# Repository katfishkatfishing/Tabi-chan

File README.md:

# Tabi-chan
>Our plan for Third Space Hack Club - Week 3!

A travel companion that tracks and logs your journey, and provides the weather data, and geo data.

## Project Overview
An adorable little travel companion that lives in a small device that has an e-ink display and a GPS sensor.

Tabi-chan (旅-chan) is a little gps sensor that you can clip onto yourself when out on a journey. She then sends over the tracked data to your phone via BLE and dislays it all on a web app. The basic features of the web app are route tracking, location overview, and weather overview. 

### <ins>Key Features of Box</ins> 
<ul style="margin-top: -5px; margin-bottom: 0; padding-left: 10px">
    <p style="margin-bottom: 5px">
        <b>GPS Tracking & Activity Logging</b>
    <ul style="padding-left: 45px">
        <p style="text-indent: -24px; margin-bottom: 5px">
            <b>GPS:</b> Calculate latitude, longitude and altitude.</p>
        <p style="text-indent: -24px; margin-bottom: 5px">
            <b>Route tracking:</b> Route tracking using Leaflet, calculates pace and distance</p>
        <p style="text-indent: -24px; margin-bottom: 5px">
            <b>Location Overview:</b> Query OpenStreetMap API to get current location.</p>
        <p style="text-indent: -24px; margin-bottom: 5px">
            <b>Weather Overview:</b> Uses Open-Meteo API to fetch weather info.</p>

### Say hi to Tabi-chan

## PCB
| Top | Bottom |
| --- | --- |
|  |  |

## Case

## BOM
| Reference | Value | Qty | Price | Source |
| :--- | :--- | :--- | :--- | :--- |
| U6 | IP5306-I2C | 1 | $0.35 | https://www.lcsc.com/product-detail/New-Arrivals_INJOINIC-IP5306-I2C_C488349.html |
| U5 | AP2112K-3.3TRG1 | 1 | $0.17 | https://jlcpcb.com/partdetail/AP2112K-3.3TRG1/C51118 |
| U2 | NEO-6M-0-001_C32413118 | 1 | $6.69 | https://jlcpcb.com/partdetail/UBLOX-NEO_6M_0001/C32413118 |
| U1 | ESP32-S3-WROOM-1(N16R8) | 1 | $3.79 | https://www.lcsc.com/product-detail/C2913202.html |
| SW1 | SW_Push | 1 | $0.02 | https://www.lcsc.com/product-detail/C318884.html |
| R12 | 1k | 1 | $0.0033 | https://www.lcsc.com/product-detail/C5362357.html |
| R8 | 2R | 1 | $0.21 | https://www.digikey.com/en/products/detail/vishay-dale/RCS08052R00FKEA/5868970 |
| R4,R5,R6,R7,R9,R10,R11 | 10k | 7 | $0.0029 | https://www.lcsc.com/product-detail/chip-resistor-surface-mount_tyohm-rmc-0603-10k-j-n_C5362358.html |
| R3 | 0.5R | 1 | $0.0013 | https://jlcpcb.com/partdetail/VO-SCR0603JR500/C3017643 |
| R1,R2 | 5.1k | 2 | $0.0016 | https://www.lcsc.com/product-detail/C23186.html |
| Q1,Q2 | BSS138BKW | 2 | RM1.10 | https://www.digikey.my/en/products/detail/nexperia-usa-inc/BSS138BKW-115/2779824 |
| L1 | 1uH | 1 | $0.0742 | https://jlcpcb.com/partdetail/YJYCOIN-YHNR30121R0M/C20416185 |
| J4 | Conn_01x08 | 1 | $0.0491 | https://www.lcsc.com/product-detail/C492407.html |
| J3 | Conn_01x02 | 1 | $0.0180 | https://www.lcsc.com/product-detail/C492401.html |
| J2 | U.FL | 1 | $0.1072 | https://www.lcsc.com/product-detail/C88374.html |
| J1 | USB_C_Receptacle_USB2.0_16P | 1 | $0.0415 | https://www.lcsc.com/product-detail/C2765186.html |
| C11,C12,C13 | 0.1uF | 3 | $0.0107 | https://www.lcsc.com/product-detail/C131394.html |
C8,C9,C10,C14 | 1uF | 4 | $0.1137 | https://jlcpcb.com/partdetail/KEMET-C0603C105K3RACTU/C2177372|
C6,C7,C15 | 10uF | 3 | $0.1027 | https://jlcpcb.com/partdetail/AIDECAPACITOR-0805X5R106M500NT/C49326683|
C1,C2,C3,C4,C5 | 22uF | 5 | $0.0844 | https://jlcpcb.com/partdetail/CCTC-TCC0805X5R226K160FT/C48885730|

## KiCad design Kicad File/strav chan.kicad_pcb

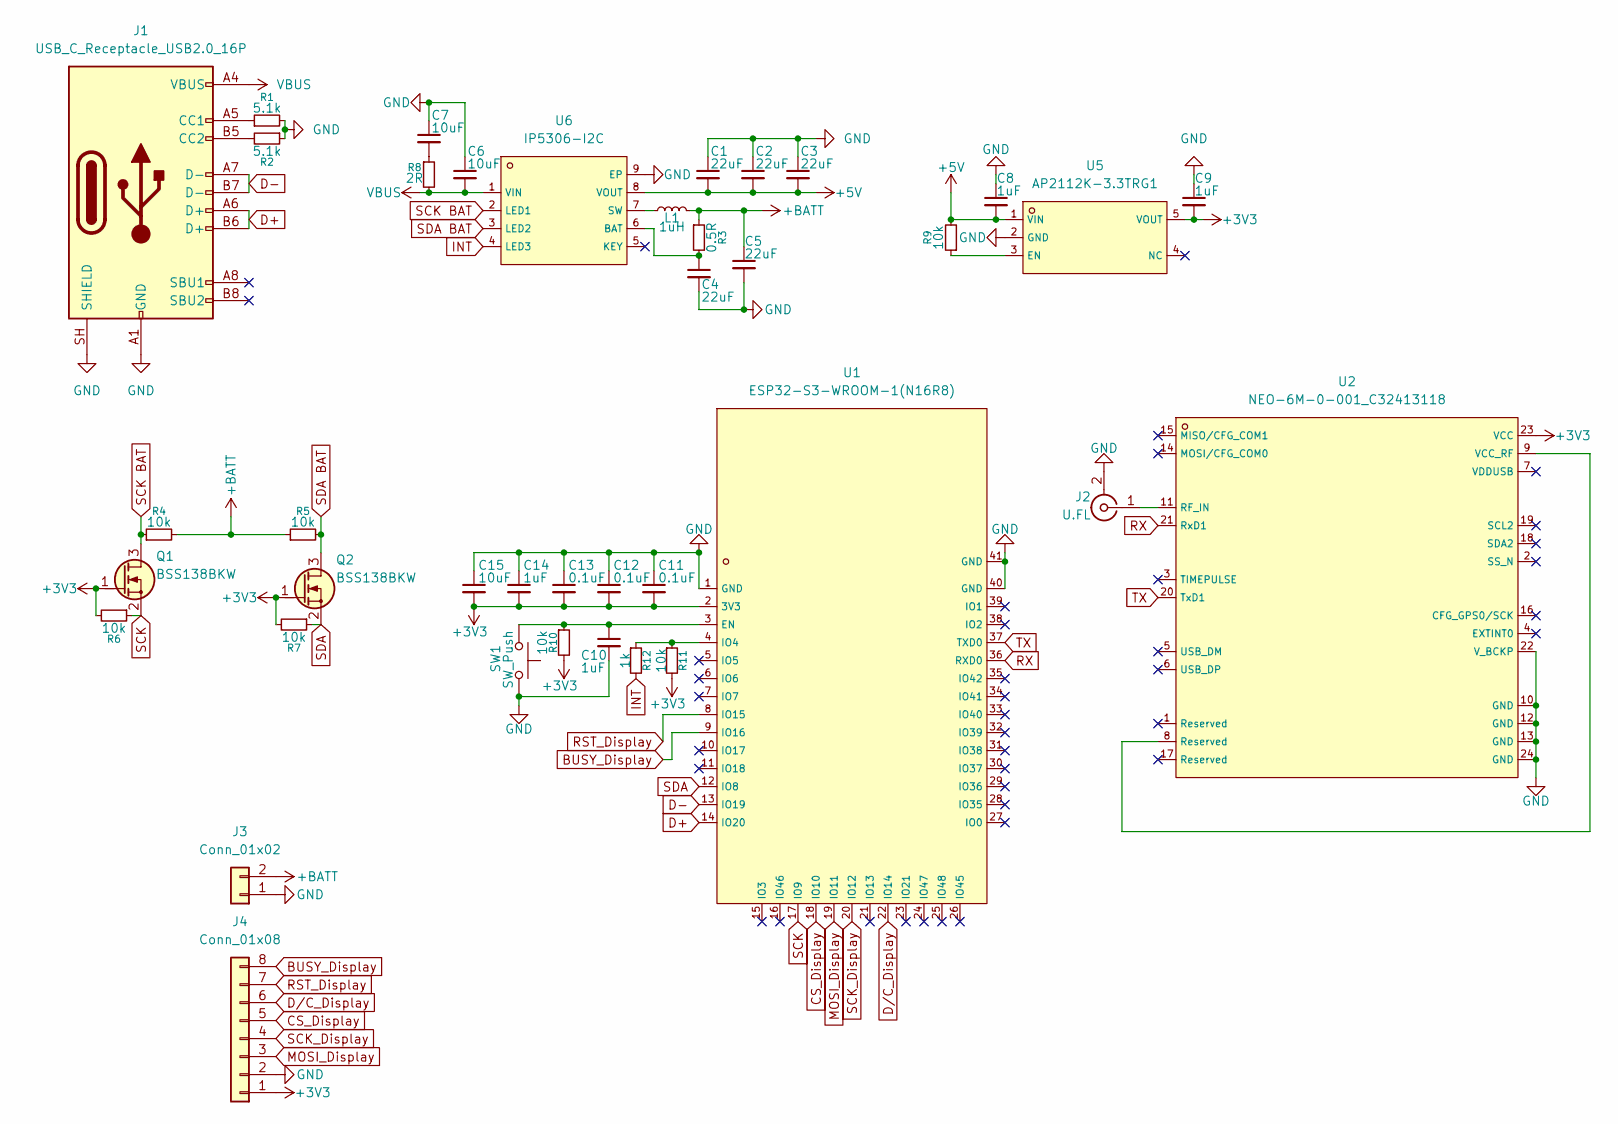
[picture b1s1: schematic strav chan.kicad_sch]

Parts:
C1, C2, C3, C4, C5: 22uF; C_0603_1608Metric_Pad1.08x0.95mm_HandSolder
C6, C7, C15: 10uF; C_0603_1608Metric_Pad1.08x0.95mm_HandSolder
C8, C9, C10, C14: 1uF; C_0402_1005Metric_Pad0.74x0.62mm_HandSolder
C11, C12, C13: 0.1uF; C_0402_1005Metric_Pad0.74x0.62mm_HandSolder
J1: USB_C_Receptacle_USB2.0_16P; USB_C_Receptacle_GCT_USB4085
J2: U.FL; IPEX-SMD_BWIPX-1-001E; LCSC C5137195
J3: Conn_01x02; JST_GH_SM02B-GHS-TB_1x02-1MP_P1.25mm_Horizontal; Part Number 1-0201FBV0T
J4: Conn_01x08; JST_GH_SM08B-GHS-TB_1x08-1MP_P1.25mm_Horizontal
L1: 1uH; L_APV_ANR4030
Q1, Q2: BSS138BKW; SOT-323_SC-70
R1, R2: 5.1k; R_0402_1005Metric_Pad0.72x0.64mm_HandSolder
R3: 0.5R; R_0402_1005Metric_Pad0.72x0.64mm_HandSolder
R4, R5, R6, R7, R9, R10, R11: 10k; R_0402_1005Metric_Pad0.72x0.64mm_HandSolder
R8: 2R; R_0402_1005Metric_Pad0.72x0.64mm_HandSolder
R12: 1k; R_0402_1005Metric_Pad0.72x0.64mm_HandSolder
SW1: SW_Push; SW_SPST_B3U-1000P
U1: ESP32-S3-WROOM-1(N16R8); C2913202_WIRELM-SMD_ESP32-S3-WROOM-1; LCSC C2913202
U2: NEO-6M-0-001_C32413118; C32413118_SMD; LCSC C32413118
U5: AP2112K-3.3TRG1; C51118_SOT-25-5_L2_9-W1_6-P0_95-LS2_8-BL; LCSC C51118
U6: IP5306-I2C; C488349_ESOP-8_L4_9-W3_9-P1_27-LS6_0-BL-EP2_0; LCSC C488349

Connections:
+3V3: C9.2, C11.2, C12.2, C13.2, C14.2, C15.2, J4.1, Q1.1 (G), Q2.1 (G), R6.2, R7.2, R10.2, R11.2, U1.2 (3V3), U2.23 (VCC), U5.5 (VOUT)
+5V: C1.2, C2.2, C3.2, C8.2, R9.2, U5.1 (VIN), U6.8 (VOUT)
+BATT: C5.1, J3.2, L1.2, R3.1, R4.2, R5.1
BUSY_Display: J4.8, U1.9 (IO16)
CS_Display: J4.5, U1.18 (IO10)
D+: J1.A6 (D+), J1.B6 (D+), U1.14 (IO20)
D-: J1.A7 (D-), J1.B7 (D-), U1.13 (IO19)
D/C_Display: J4.6, U1.22 (IO14)
GND: C1.1, C2.1, C3.1, C4.2, C5.2, C6.1, C7.1, C8.1, C9.1, C10.2, C11.1, C12.1, C13.1, C14.1, C15.1, J1.A1 (GND), J1.A12 (GND), J1.B1 (GND), J1.B12 (GND), J1.SH (SHIELD), J2.2 (Ext), J3.1, J4.2, R1.2, R2.1, SW1.2, U1.1 (GND), U1.40 (GND), U1.41 (GND), U2.10 (GND), U2.12 (GND), U2.13 (GND), U2.22 (V_BCKP), U2.24 (GND), U5.2 (GND), U6.9 (EP)
INT: R12.2, U6.4 (LED3)
MOSI_Display: J4.3, U1.19 (IO11)
unnamed: C7.2, R8.1
unnamed: J1.A5 (CC1), R1.1
unnamed: J1.B5 (CC2), R2.2
unnamed: J2.1 (In), U2.11 (RF_IN)
unnamed: C10.1, R10.1, SW1.1, U1.3 (EN)
unnamed: R11.1, R12.1, U1.4 (IO4)
unnamed: U2.8 (Reserved), U2.9 (VCC_RF)
unnamed: R9.1, U5.3 (EN)
unnamed: C4.1, R3.2, U6.6 (BAT)
unnamed: L1.1, U6.7 (SW)
RST_Display: J4.7, U1.8 (IO15)
RX: U1.36 (RXD0), U2.21 (RxD1)
SCK: Q1.2 (S), R6.1, U1.17 (IO9)
SCK BAT: Q1.3 (D), R4.1, U6.2 (LED1)
SCK_Display: J4.4, U1.20 (IO12)
SDA: Q2.2 (S), R7.1, U1.12 (IO8)
SDA BAT: Q2.3 (D), R5.2, U6.3 (LED2)
TX: U1.37 (TXD0), U2.20 (TxD1)
VBUS: C6.2, J1.A4 (VBUS), J1.A9 (VBUS), J1.B4 (VBUS), J1.B9 (VBUS), R8.2, U6.1 (VIN)

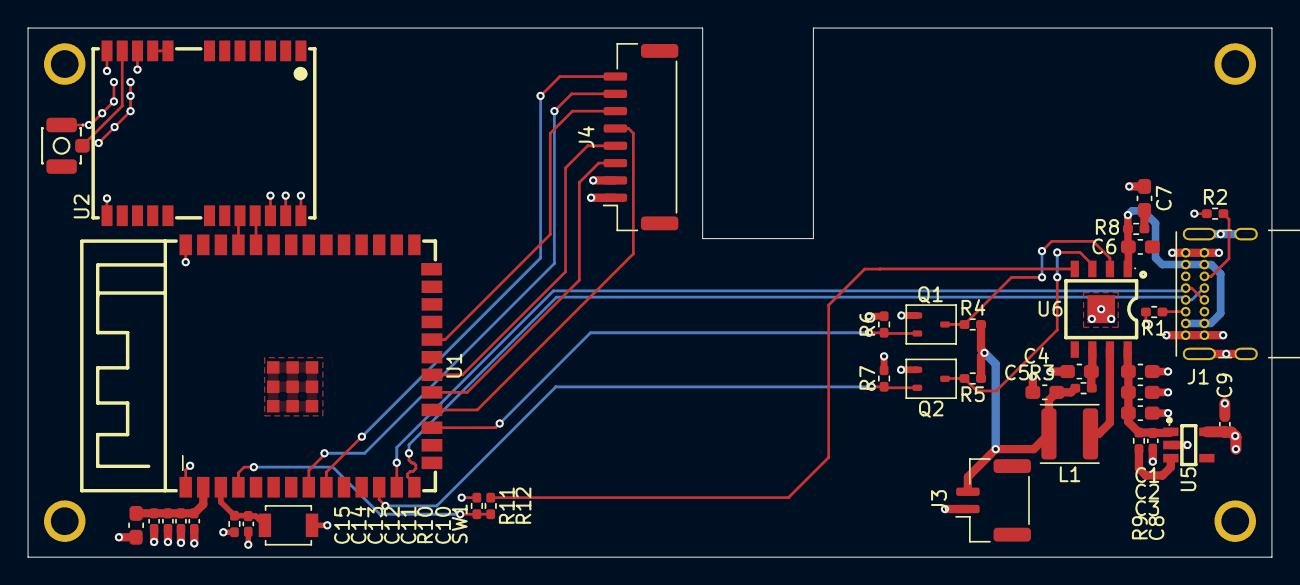
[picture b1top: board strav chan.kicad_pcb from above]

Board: 4 copper layers, 89.8 x 38.2 mm, 39 parts (0 on the bottom side), 30 nets.

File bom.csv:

Reference,Value,Qty,Price,Source
U6,IP5306-I2C,1,"$0.35",LCSC C488349
U5,AP2112K-3.3TRG1,1,$0.17,JLCPCB C51118
U2,NEO-6M-0-001_C32413118,1,$6.69,JLCPCB C32413118
U1,ESP32-S3-WROOM-1(N16R8),1,$3.79,LCSC C2913202
SW1,SW_Push,1,"$0.02",LCSC C318884
R12,1k,1,"$0.0033",LCSC C5362357
R8,2R,1,$0.21,DigiKey RCS08052R00FKEA
"R4-R7, R9-R11",10k,7,"$0.0029",LCSC C5362358
R3,0.5R,1,"$0.0013",JLCPCB C3017643
"R1, R2",5.1k,2,"$0.0016",LCSC C23186
"Q1, Q2",BSS138BKW,2,RM1.10,DigiKey MY BSS138BKW-115
L1,1uH,1,$0.0742,JLCPCB C20416185
J4,Conn_01x08,1,"$0.0491",LCSC C492407
J3,Conn_01x02,1,"$0.0180",LCSC C492401
J2,U.FL,1,"$0.1072",LCSC C88374
J1,USB_C_Receptacle_USB2.0_16P,1,$0.0415,LCSC C2765186
C11-C13,0.1uF,3,"$0.0107",LCSC C131394
"C8-C10, C14",1uF,4,$0.1137,JLCPCB C2177372
"C6, C7, C15",10uF,3,$0.1027,JLCPCB C49326683
C1-C5,22uF,5,$0.0844,JLCPCB C488857300
